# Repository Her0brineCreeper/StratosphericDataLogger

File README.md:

# StratosphericDataLogger
This repository contains the design and source code of the Stratospheric Data Logger developed by Bryan Hoxha during the European Project Semester 2025 at Politehnica Bucharest.
It was developed to log the measurements of a number of sensors onto a microSD card during a stratospheric balloon flight.
# Hardware
- ESP32 microcontroller (a FireBeetle 2 ESP32-E was used for this project)
- 2x BME280 for inside and outside the payload
- MS5611 pressure sensor (inside)
- SCD41 CO₂ sensor (inside)
- SI1145 light/UV sensor (outside)
- RCB-09T-01 GPS module (other GPS modules should work fine as well)
- SPI microSD card module
- custom-made PCB (made in KiCad v8) with modular design and two extra outputs (I²C) for additional sensors
- one of which was used for an MPU6050 accelerometer/gyroscope (inside)
# Software
- made in Arduino IDE
- logs sensor measurements to a CSV file and outputs them to Serial Monitor
- Sensors are hot pluggable during operation because their presence is checked during every measurement cycle.

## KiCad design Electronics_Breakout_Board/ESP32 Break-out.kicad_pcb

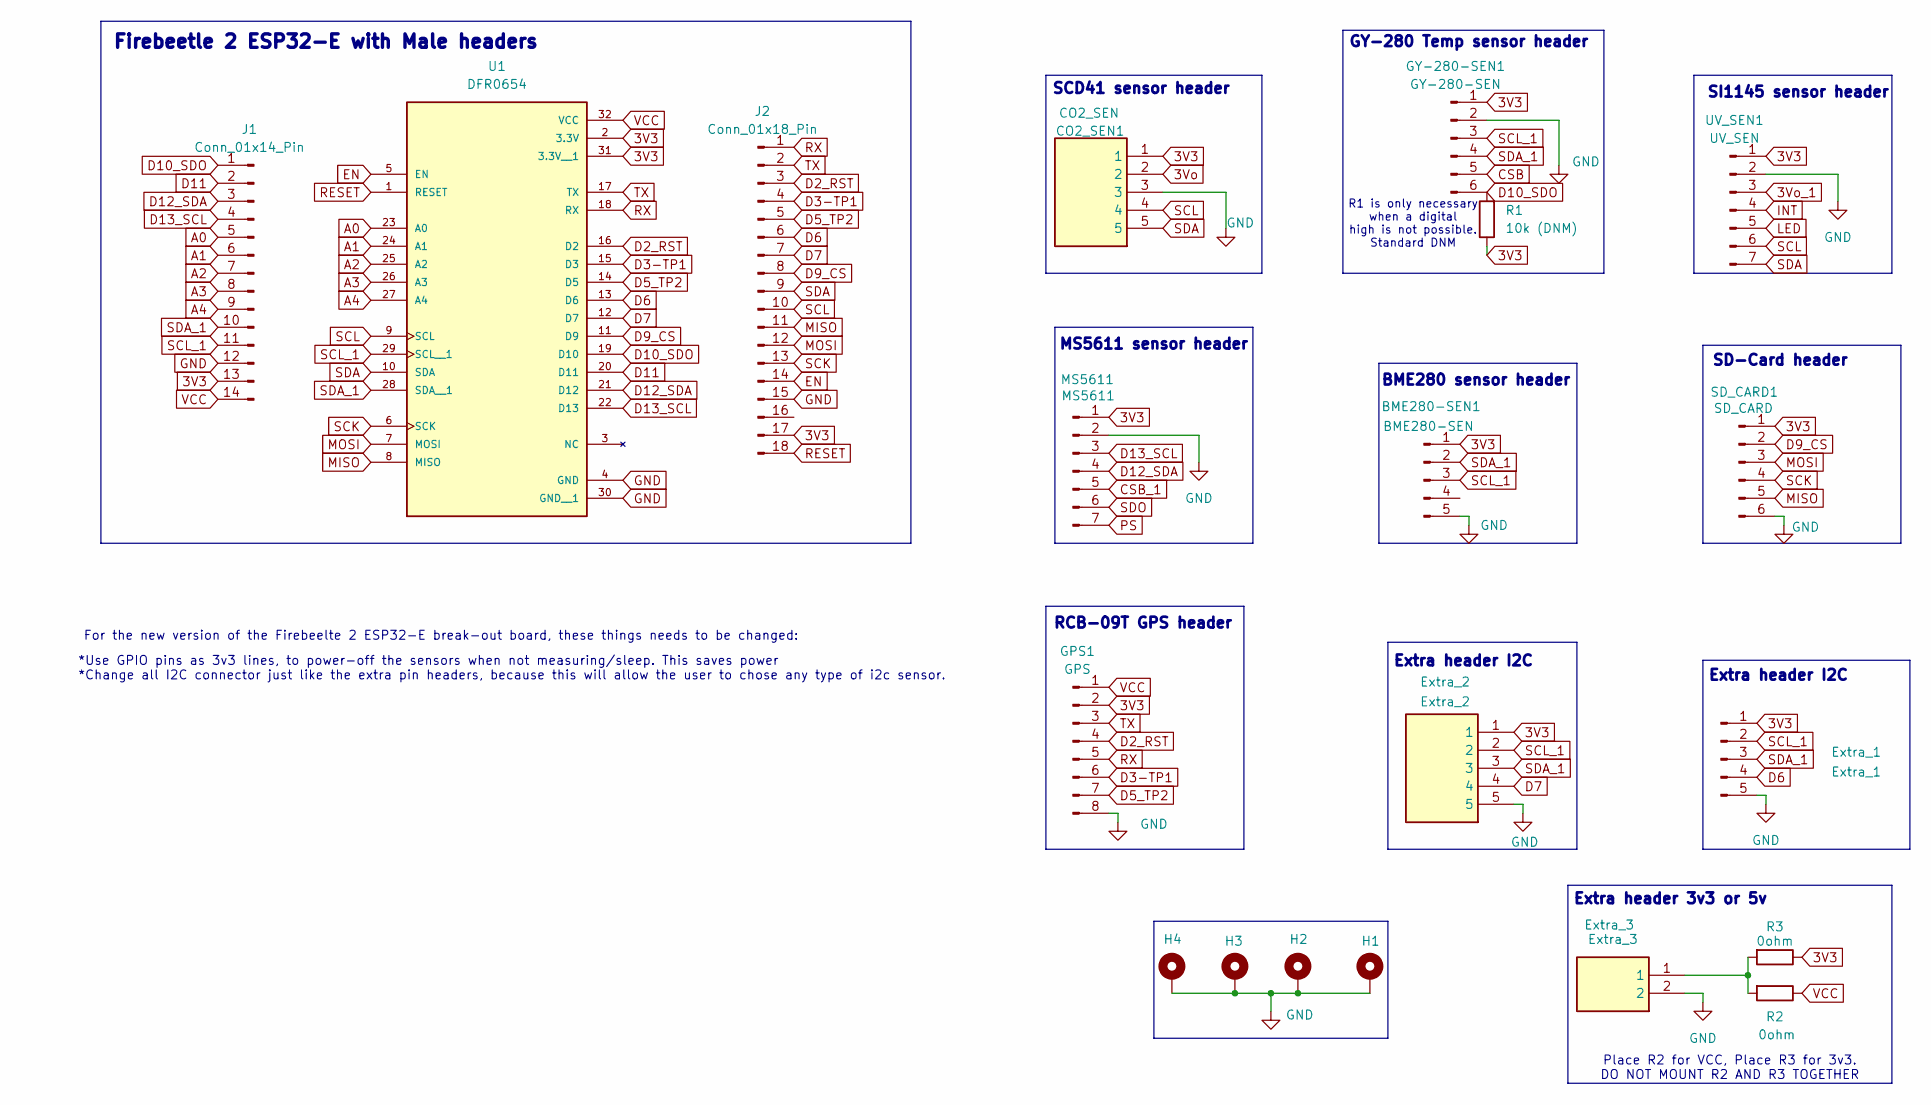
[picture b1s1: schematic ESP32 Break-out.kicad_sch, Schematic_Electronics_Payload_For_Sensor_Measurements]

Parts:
BME280-SEN1: BME280-SEN; 2200970571
CO2_SEN1: CO2_SEN; 2200970571; Manufacturer_Part_Number 220097-0571
Extra_1: Extra_1; 2200970571; Manufacturer_Part_Number 220097-0571
Extra_2: Extra_2; 2200970571; Manufacturer_Part_Number 220097-0571
Extra_3: Extra_3; 2200970271; Manufacturer_Part_Number 220097-0271; Mouser Part Number 538-220097-0271
GPS1: GPS; 2200970871
GY-280-SEN1: GY-280-SEN; 2200970671
H1, H2, H3, H4: MountingHole_Pad; MountingHole_2.2mm_M2_DIN965_Pad
J1: Conn_01x14_Pin; PinHeader_1x14_P2.54mm_Vertical
J2: Conn_01x18_Pin; PinHeader_1x18_P2.54mm_Vertical
MS5611: MS5611; CONN_2200970000-SD_07_MOL
R1: 10k (DNM); C_0805_2012Metric
R2, R3: 0ohm; C_0805_2012Metric
SD_CARD1: SD_CARD; 2200970671
U1: DFR0654; MODULE_DFR0654
UV_SEN1: UV_SEN; CONN_2200970000-SD_07_MOL

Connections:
3V3: BME280-SEN1.1, CO2_SEN1.1, Extra_1.1, Extra_2.1, GPS1.2, GY-280-SEN1.1, J1.13, J2.17, MS5611.1, R1.1, R3.1, SD_CARD1.1, U1.2 (3.3V), U1.31 (3.3V__1), UV_SEN1.1
3Vo: CO2_SEN1.2
3Vo_1: UV_SEN1.3
A0: J1.5, U1.23 (A0)
A1: J1.6, U1.24 (A1)
A2: J1.7, U1.25 (A2)
A3: J1.8, U1.26 (A3)
A4: J1.9, U1.27 (A4)
CSB: GY-280-SEN1.5
CSB_1: MS5611.5
D2_RST: GPS1.4, J2.3, U1.16 (D2)
D3-TP1: GPS1.6, J2.4, U1.15 (D3)
D5_TP2: GPS1.7, J2.5, U1.14 (D5)
D6: Extra_1.4, J2.6, U1.13 (D6)
D7: Extra_2.4, J2.7, U1.12 (D7)
D9_CS: J2.8, SD_CARD1.2, U1.11 (D9)
D10_SDO: GY-280-SEN1.6, J1.1, R1.2, U1.19 (D10)
D11: J1.2, U1.20 (D11)
D12_SDA: J1.3, MS5611.4, U1.21 (D12)
D13_SCL: J1.4, MS5611.3, U1.22 (D13)
EN: J2.14, U1.5 (EN)
GND: BME280-SEN1.5, CO2_SEN1.3, Extra_1.5, Extra_2.5, Extra_3.2, GPS1.8, GY-280-SEN1.2, H1.1, H2.1, H3.1, H4.1, J1.12, J2.15, MS5611.2, SD_CARD1.6, U1.4 (GND), U1.30 (GND__1), UV_SEN1.2
INT: UV_SEN1.4
LED: UV_SEN1.5
MISO: J2.11, SD_CARD1.5, U1.8 (MISO)
MOSI: J2.12, SD_CARD1.3, U1.7 (MOSI)
unnamed: Extra_3.1, R2.2, R3.2
PS: MS5611.7
RESET: J2.18, U1.1 (RESET)
RX: GPS1.5, J2.1, U1.18 (RX)
SCK: J2.13, SD_CARD1.4, U1.6 (SCK)
SCL: CO2_SEN1.4, J2.10, U1.9 (SCL), UV_SEN1.6
SCL_1: BME280-SEN1.3, Extra_1.2, Extra_2.2, GY-280-SEN1.3, J1.11, U1.29 (SCL__1)
SDA: CO2_SEN1.5, J2.9, U1.10 (SDA), UV_SEN1.7
SDA_1: BME280-SEN1.2, Extra_1.3, Extra_2.3, GY-280-SEN1.4, J1.10, U1.28 (SDA__1)
SDO: MS5611.6
TX: GPS1.3, J2.2, U1.17 (TX)
VCC: GPS1.1, J1.14, R2.1, U1.32 (VCC)

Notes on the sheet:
MS5611 sensor header
*Use GPIO pins as 3v3 lines, to power-off the sensors when not measuring/sleep. This saves power *Change all I2C connector just like the extra pin headers, because this will allow the user to chose any type of i2c sensor.
For the new version of the Firebeelte 2 ESP32-E break-out board, these things needs to be changed:
SCD41 sensor header
RCB-09T GPS header
SI1145 sensor header
GY-280 Temp sensor header
Extra header I2C
Firebeetle 2 ESP32-E with Male headers
BME280 sensor header
Extra header 3v3 or 5v
R1 is only necessary when a digital high is not possible. Standard DNM
SD-Card header
Place R2 for VCC, Place R3 for 3v3. DO NOT MOUNT R2 AND R3 TOGETHER

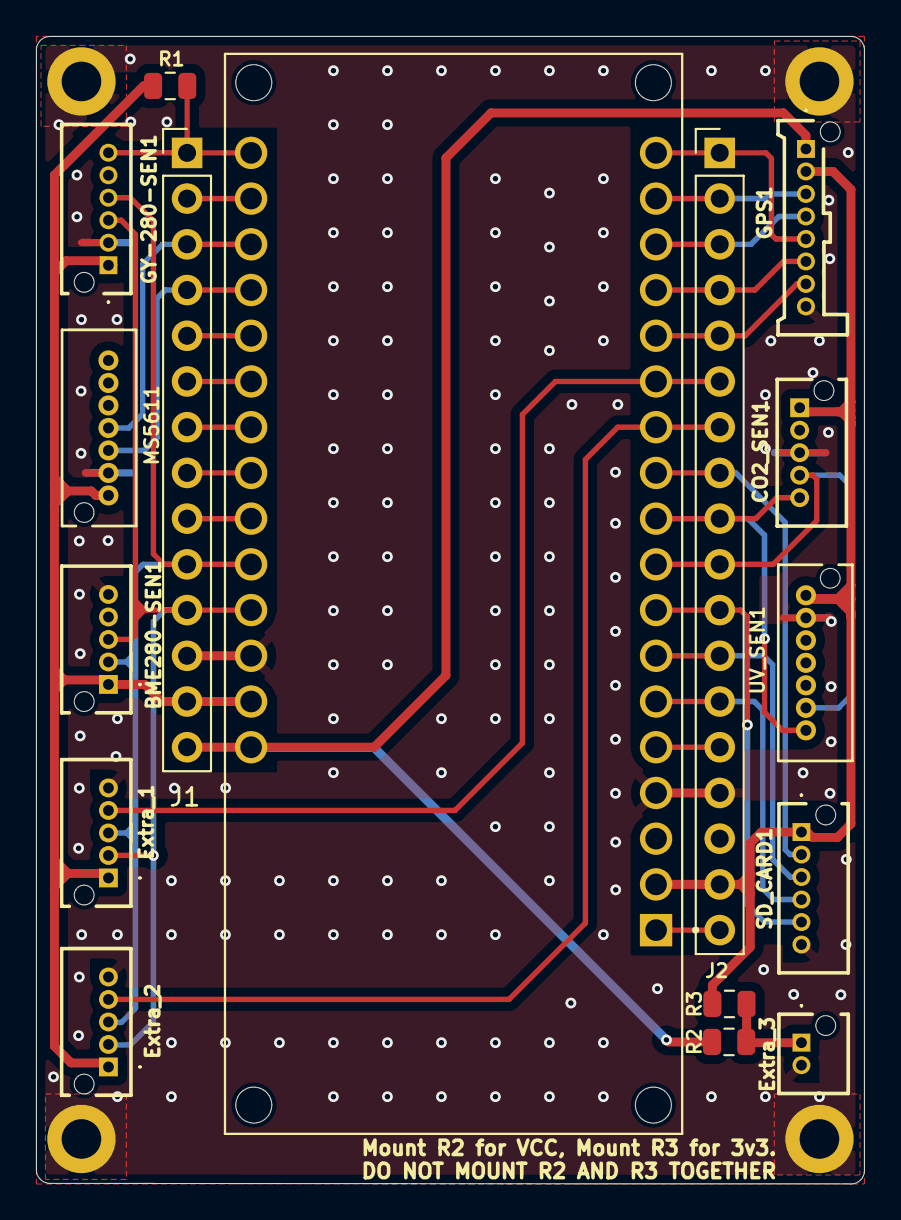
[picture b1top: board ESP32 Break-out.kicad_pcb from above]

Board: 2 copper layers, 46.0 x 63.8 mm, 20 parts (0 on the bottom side), 30 nets.

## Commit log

2025-06-09 Add source code
2025-06-09 Add schematic and PCB design
